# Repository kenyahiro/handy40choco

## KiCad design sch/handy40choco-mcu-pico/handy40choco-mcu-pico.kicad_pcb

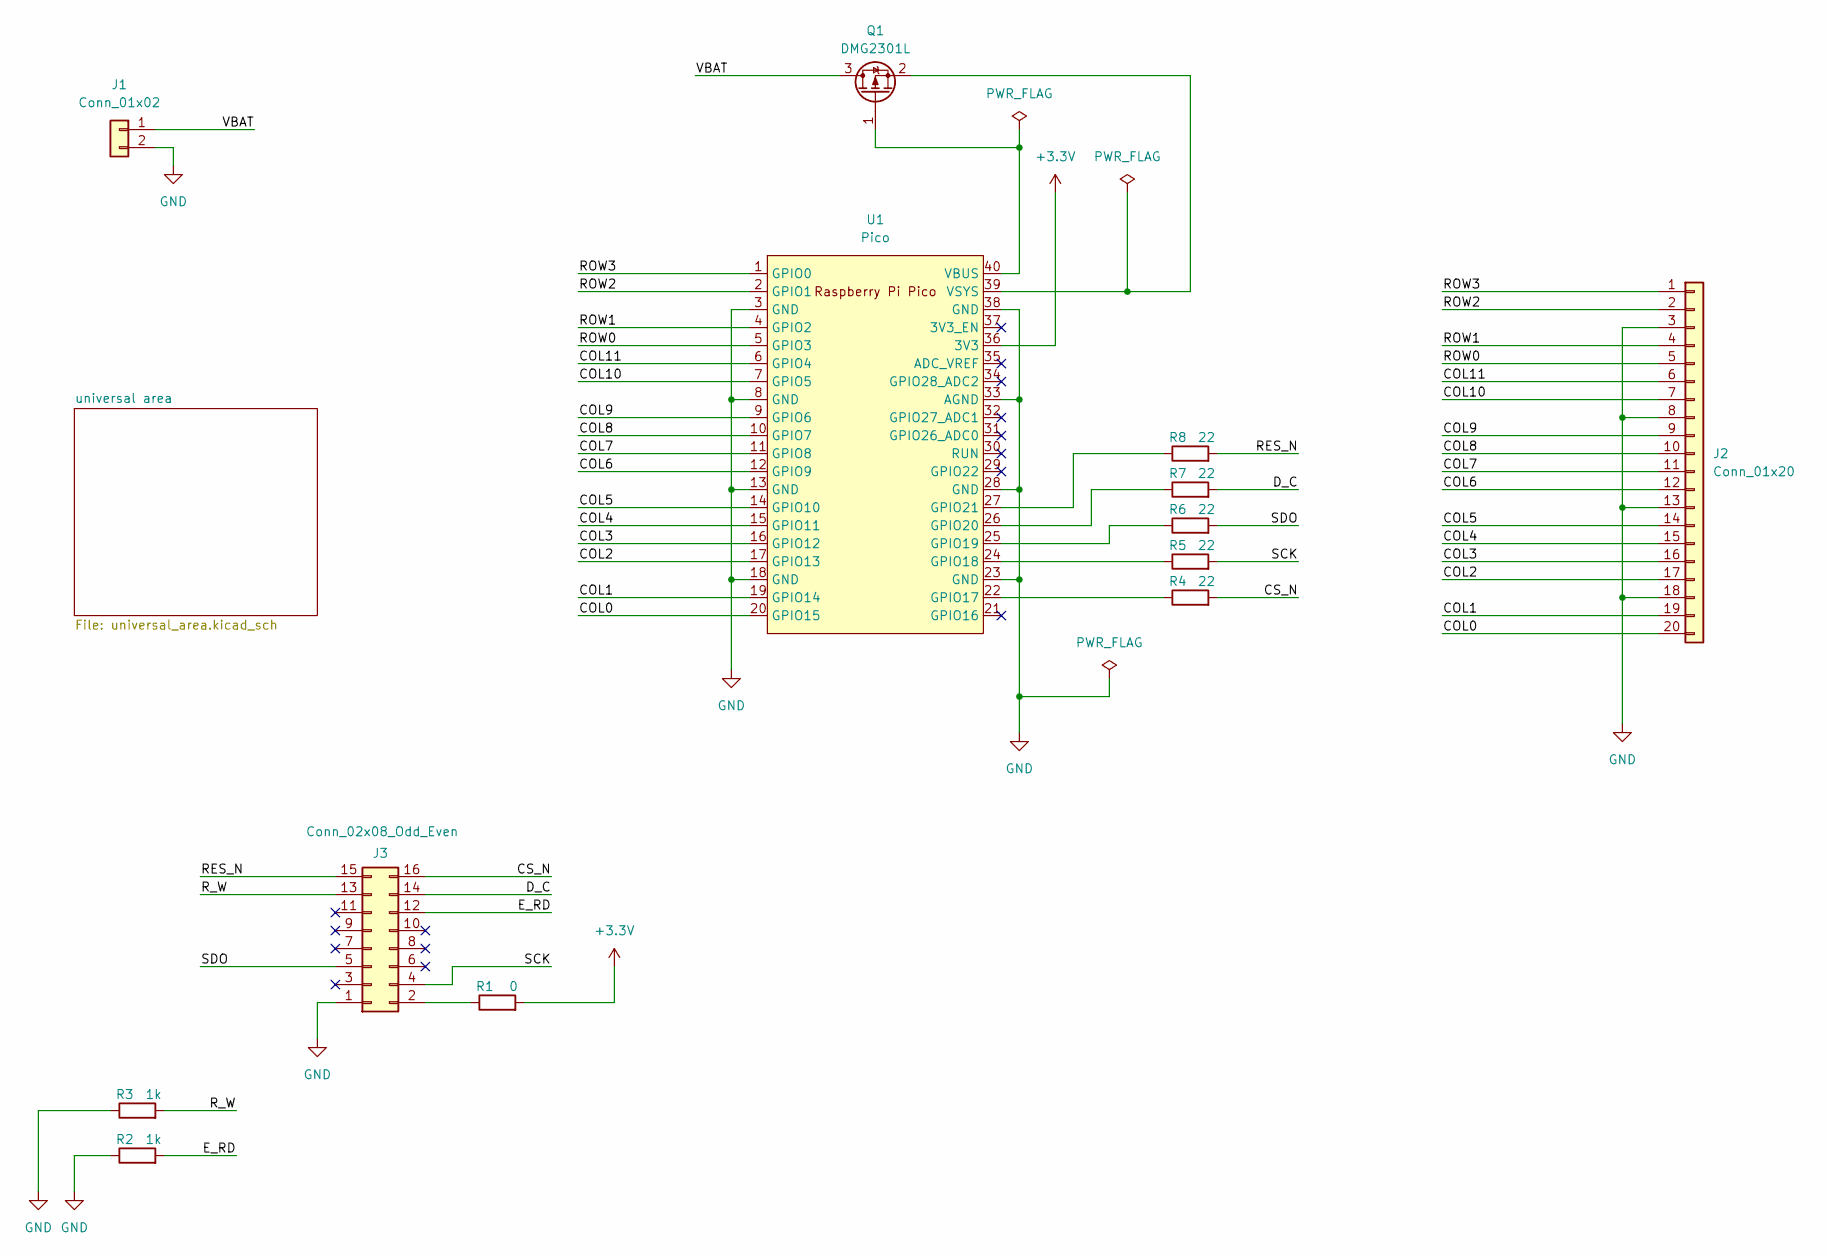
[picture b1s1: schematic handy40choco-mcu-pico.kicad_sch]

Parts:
J1: Conn_01x02; JST_PH_B2B-PH-K_1x02_P2.00mm_Vertical
J2: Conn_01x20; my_PinHeader_1x20_P2.54mm_Vertical_p0.85
J3: Conn_02x08_Odd_Even; oled_PinSocket_2x08_P2.54mm_Vertical
Q1: DMG2301L; SOT-23
R1: 0; R_0603_1608Metric_Pad0.98x0.95mm_HandSolder
R2, R3: 1k; R_0603_1608Metric_Pad0.98x0.95mm_HandSolder
R4, R5, R6, R7, R8: 22; R_0603_1608Metric_Pad0.98x0.95mm_HandSolder
U1: Pico; pico_no_dbg_smd_th_p0.85

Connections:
+3.3V: R1.2, U1.36 (3V3)
/COL0: J2.20, U1.20 (GPIO15)
/COL1: J2.19, U1.19 (GPIO14)
/COL2: J2.17, U1.17 (GPIO13)
/COL3: J2.16, U1.16 (GPIO12)
/COL4: J2.15, U1.15 (GPIO11)
/COL5: J2.14, U1.14 (GPIO10)
/COL6: J2.12, U1.12 (GPIO9)
/COL7: J2.11, U1.11 (GPIO8)
/COL8: J2.10, U1.10 (GPIO7)
/COL9: J2.9, U1.9 (GPIO6)
/COL10: J2.7, U1.7 (GPIO5)
/COL11: J2.6, U1.6 (GPIO4)
/CS_N: J3.16, R4.2
/D_C: J3.14, R7.2
/E_RD: J3.12, R2.2
/RES_N: J3.15, R8.2
/ROW0: J2.5, U1.5 (GPIO3)
/ROW1: J2.4, U1.4 (GPIO2)
/ROW2: J2.2, U1.2 (GPIO1)
/ROW3: J2.1, U1.1 (GPIO0)
/R_W: J3.13, R3.2
/SCK: J3.4, R5.2
/SDO: J3.5, R6.2
/VBAT: J1.1, Q1.3 (D)
GND: J1.2, J2.3, J2.8, J2.13, J2.18, J3.1, R2.1, R3.1, U1.3 (GND), U1.8 (GND), U1.13 (GND), U1.18 (GND), U1.23 (GND), U1.28 (GND), U1.33 (AGND), U1.38 (GND)
unnamed: J3.2, R1.1
unnamed: Q1.1 (G), U1.40 (VBUS)
unnamed: Q1.2 (S), U1.39 (VSYS)
unnamed: R4.1, U1.22 (GPIO17)
unnamed: R5.1, U1.24 (GPIO18)
unnamed: R6.1, U1.25 (GPIO19)
unnamed: R7.1, U1.26 (GPIO20)
unnamed: R8.1, U1.27 (GPIO21)

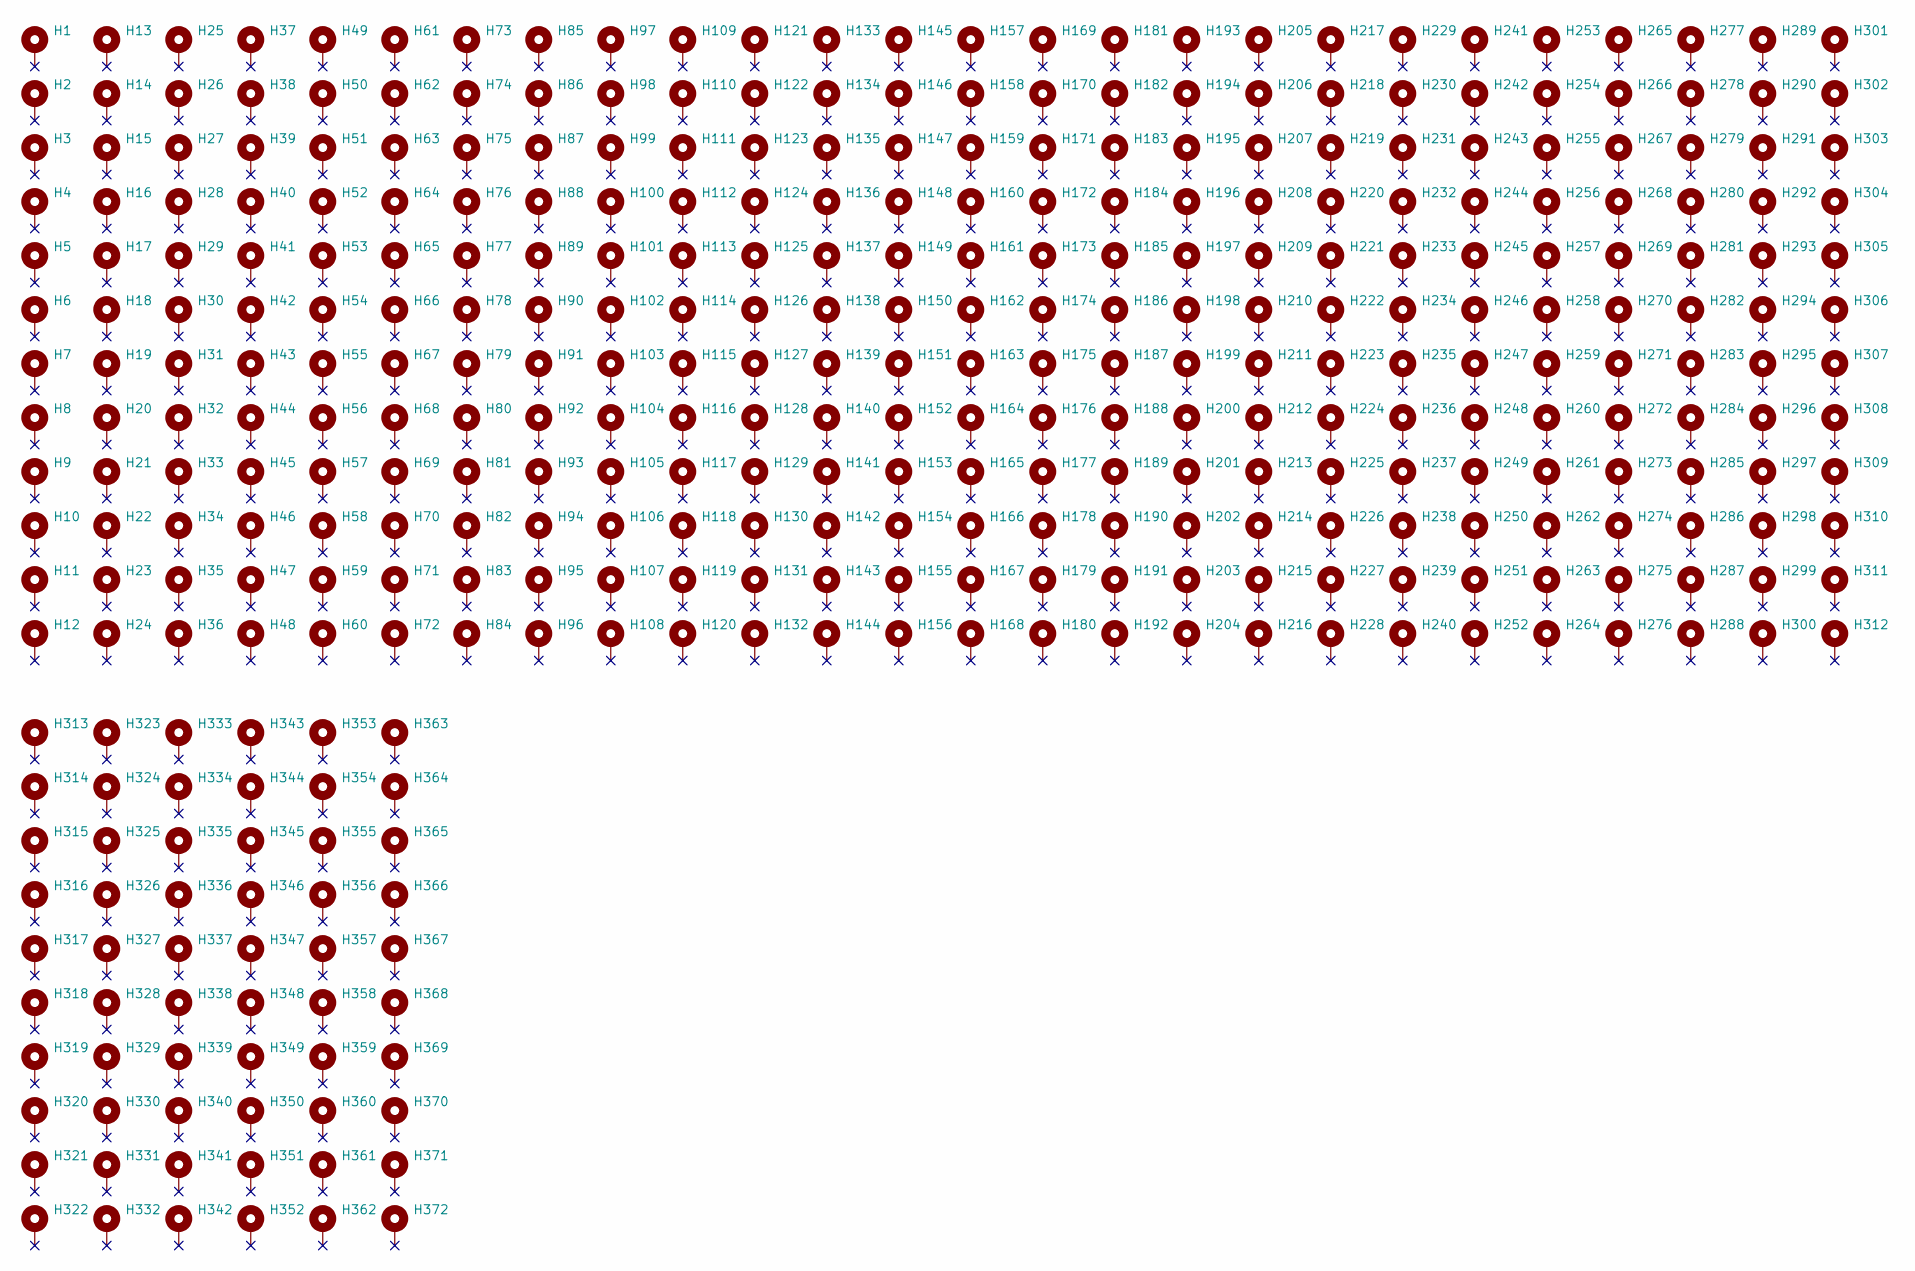
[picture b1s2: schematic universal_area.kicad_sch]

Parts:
H1, H2, H3, H4, H5, H6, H7, H8, H9, H10, H11, H12, H13, H14, H15, H16, H17, H18, H19, H20, H21, H22, H23, H24, H25, H26, H27, H28, H29, H30, H31, H32, H33, H34, H35, H36, H37, H38, H39, H40, H41, H42, H43, H44, H45, H46, H47, H48, H49, H50, H51, H52, H53, H54, H55, H56, H57, H58, H59, H60, H61, H62, H63, H64, H65, H66, H67, H68, H69, H70, H71, H72, H73, H74, H75, H76, H77, H78, H79, H80, H81, H82, H83, H84, H85, H86, H87, H88, H89, H90, H91, H92, H93, H94, H95, H96, H97, H98, H99, H100, H101, H102, H103, H104, H105, H106, H107, H108, H109, H110, H111, H112, H113, H114, H115, H116, H117, H118, H119, H120, H121, H122, H123, H124, H125, H126, H127, H128, H129, H130, H131, H132, H133, H134, H135, H136, H137, H138, H139, H140, H141, H142, H143, H144, H145, H146, H147, H148, H149, H150, H151, H152, H153, H154, H155, H156, H157, H158, H159, H160, H161, H162, H163, H164, H165, H166, H167, H168, H169, H170, H171, H172, H173, H174, H175, H176, H177, H178, H179, H180, H181, H182, H183, H184, H185, H186, H187, H188, H189, H190, H191, H192, H193, H194, H195, H196, H197, H198, H199, H200, H201, H202, H203, H204, H205, H206, H207, H208, H209, H210, H211, H212, H213, H214, H215, H216, H217, H218, H219, H220, H221, H222, H223, H224, H225, H226, H227, H228, H229, H230, H231, H232, H233, H234, H235, H236, H237, H238, H239, H240, H241, H242, H243, H244, H245, H246, H247, H248, H249, H250, H251, H252, H253, H254, H255, H256, H257, H258, H259, H260, H261, H262, H263, H264, H265, H266, H267, H268, H269, H270, H271, H272, H273, H274, H275, H276, H277, H278, H279, H280, H281, H282, H283, H284, H285, H286, H287, H288, H289, H290, H291, H292, H293, H294, H295, H296, H297, H298, H299, H300, H301, H302, H303, H304, H305, H306, H307, H308, H309, H310, H311, H312, H313, H314, H315, H316, H317, H318, H319, H320, H321, H322, H323, H324, H325, H326, H327, H328, H329, H330, H331, H332, H333, H334, H335, H336, H337, H338, H339, H340, H341, H342, H343, H344, H345, H346, H347, H348, H349, H350, H351, H352, H353, H354, H355, H356, H357, H358, H359, H360, H361, H362, H363, H364, H365, H366, H367, H368, H369, H370, H371, H372: MountingHole_Pad; TestPoint_THTPad_a

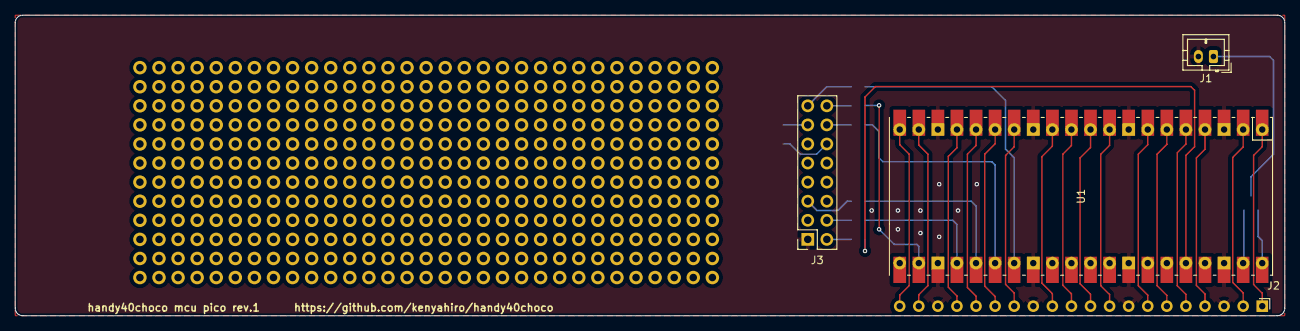
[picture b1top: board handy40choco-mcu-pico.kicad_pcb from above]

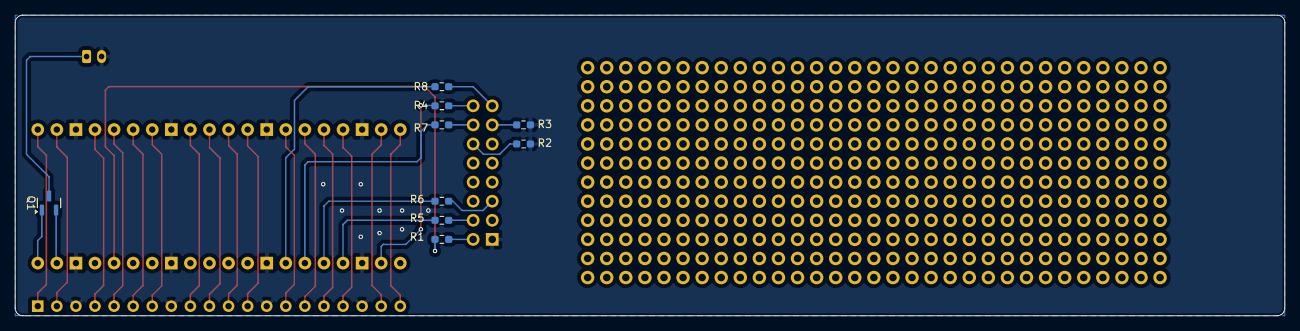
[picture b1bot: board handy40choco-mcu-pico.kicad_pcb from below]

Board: 2 copper layers, 169.0 x 40.0 mm, 385 parts (9 on the bottom side), 34 nets.

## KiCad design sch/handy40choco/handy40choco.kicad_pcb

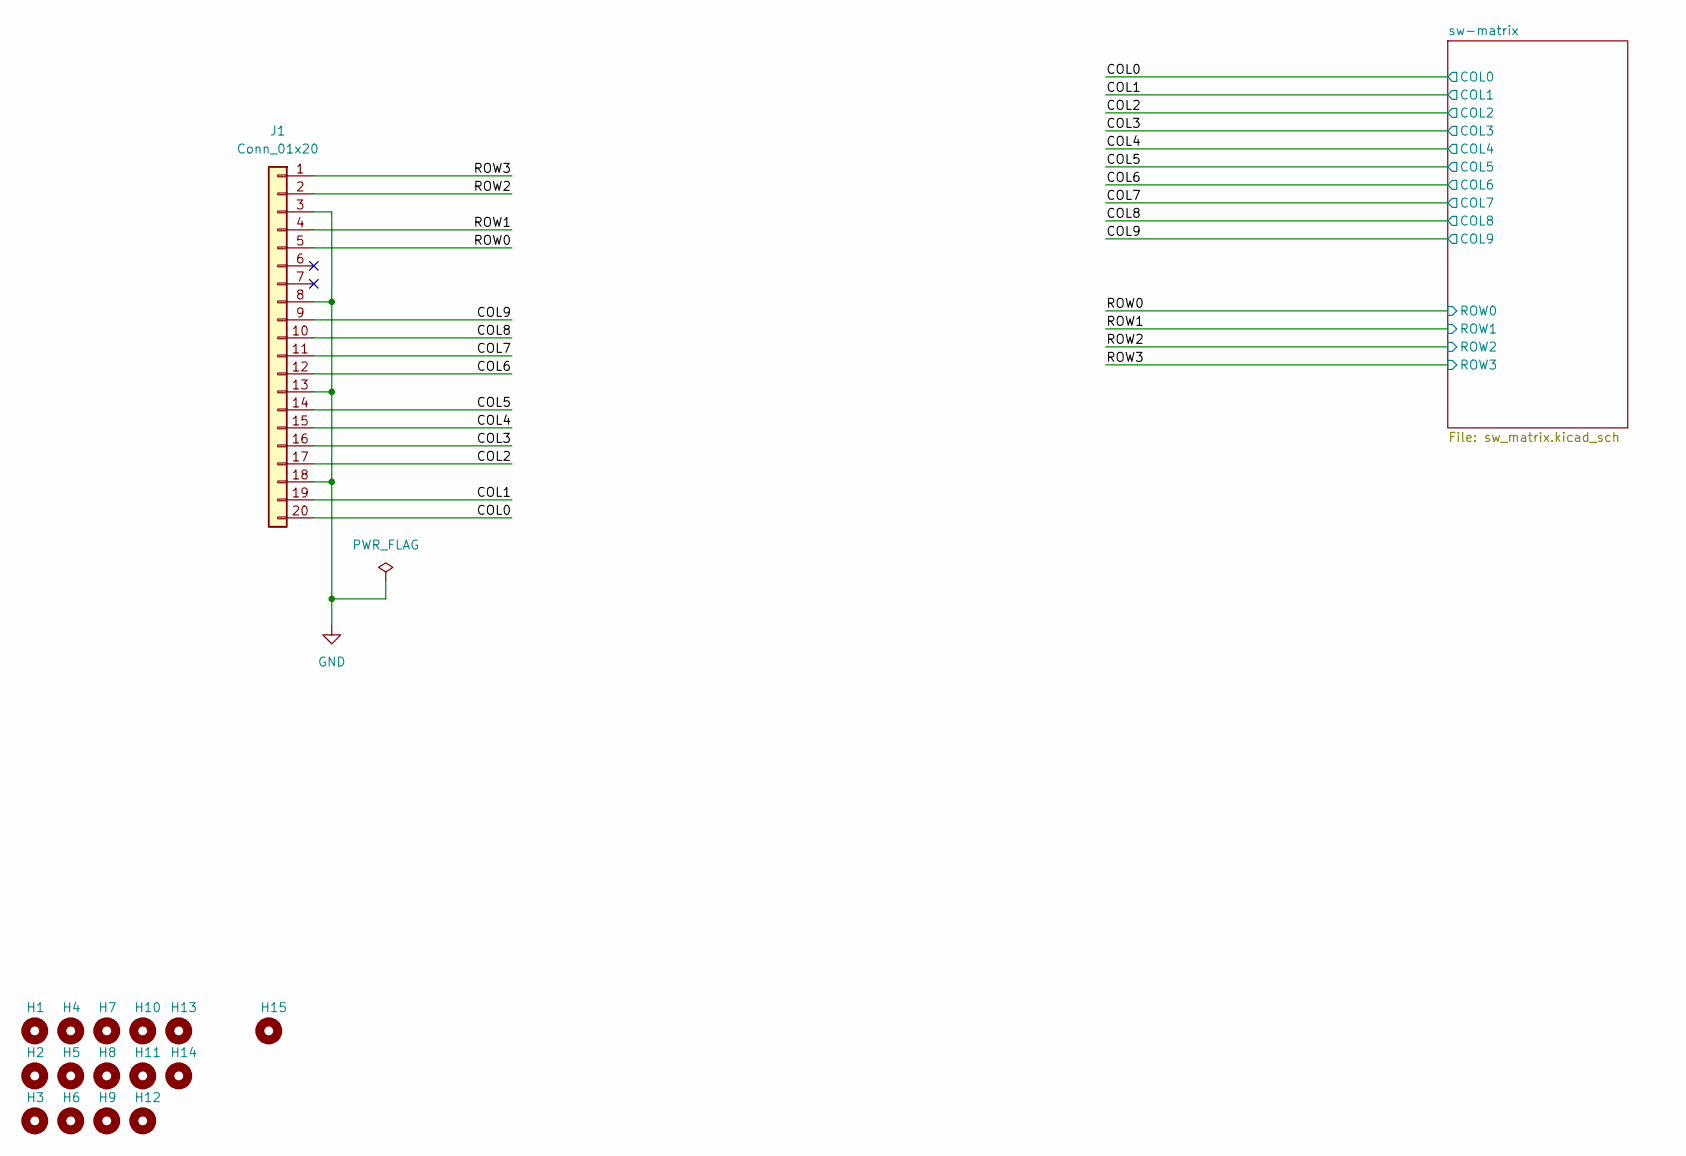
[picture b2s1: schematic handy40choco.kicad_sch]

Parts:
H1, H2, H3, H4, H5, H6, H7, H8, H9, H10, H11, H12, H13, H14, H15: MountingHole; my_MountingHole_2.2mm_M2
J1: Conn_01x20; my_PinHeader_1x20_P2.54mm_Vertical_p0.85

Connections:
/COL0: J1.20; also elsewhere on the board
/COL1: J1.19; also elsewhere on the board
/COL2: J1.17; also elsewhere on the board
/COL3: J1.16; also elsewhere on the board
/COL4: J1.15; also elsewhere on the board
/COL5: J1.14; also elsewhere on the board
/COL6: J1.12; also elsewhere on the board
/COL7: J1.11; also elsewhere on the board
/COL8: J1.10; also elsewhere on the board
/COL9: J1.9; also elsewhere on the board
/ROW0: J1.5; also elsewhere on the board
/ROW1: J1.4; also elsewhere on the board
/ROW2: J1.2; also elsewhere on the board
/ROW3: J1.1; also elsewhere on the board
GND: J1.3, J1.8, J1.13, J1.18

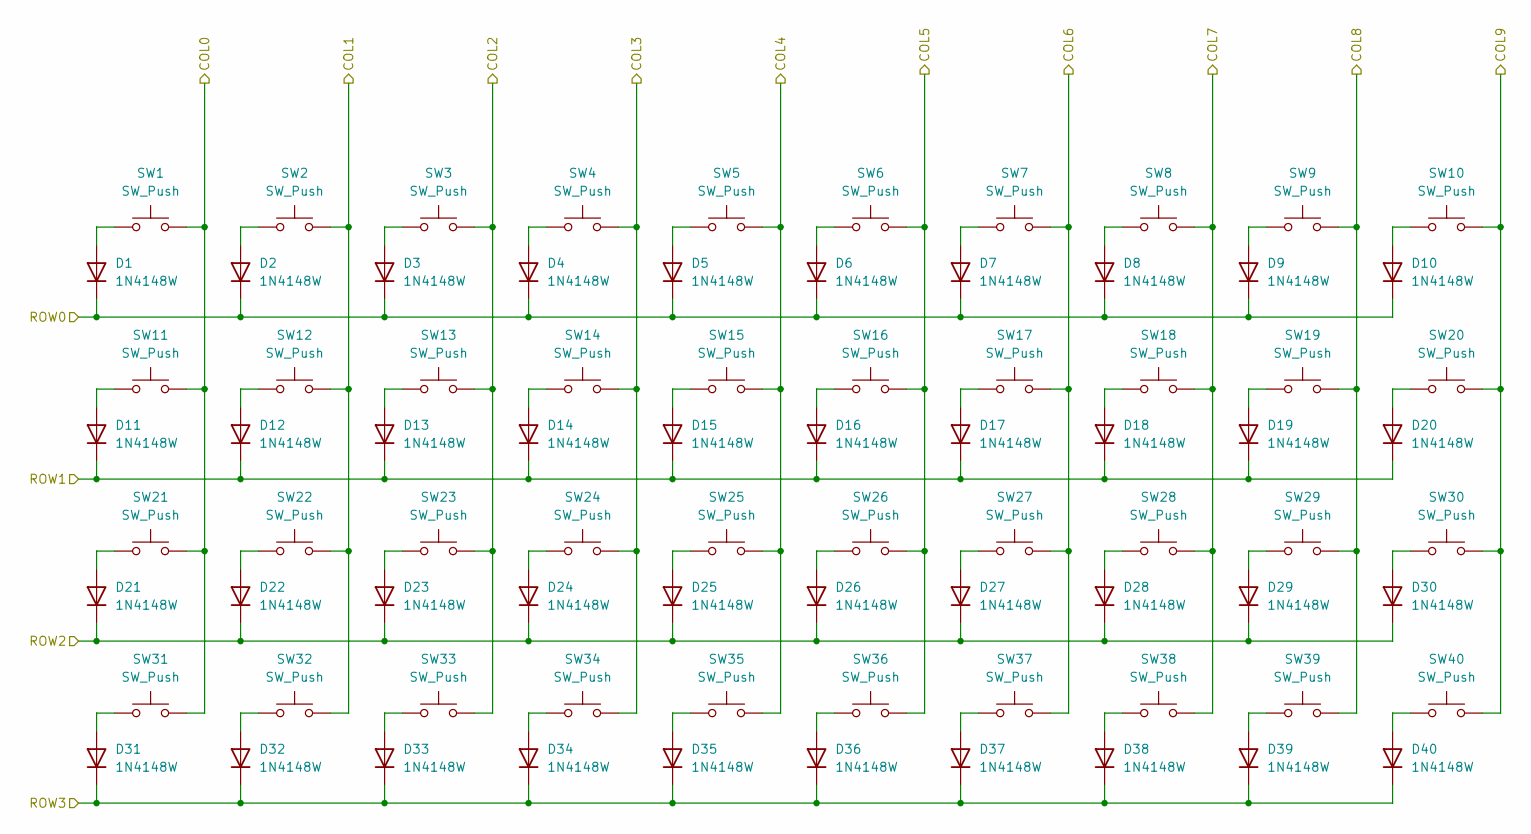
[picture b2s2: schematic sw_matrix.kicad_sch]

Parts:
D1, D2, D3, D4, D5, D6, D7, D8, D9, D10, D11, D12, D13, D14, D15, D16, D17, D18, D19, D20, D21, D22, D23, D24, D25, D26, D27, D28, D29, D30, D31, D32, D33, D34, D35, D36, D37, D38, D39, D40: 1N4148W; D_SOD-123
SW1, SW2, SW3, SW4, SW5, SW6, SW7, SW8, SW9, SW10, SW11, SW12, SW13, SW14, SW15, SW16, SW17, SW18, SW19, SW20, SW21, SW22, SW23, SW24, SW25, SW26, SW27, SW28, SW29, SW30, SW31, SW32, SW33, SW34, SW35, SW36, SW37, SW38, SW39, SW40: SW_Push; SW_Hotswap_Kailh_Choc_V1V2_no_mp

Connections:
/COL0: SW1.1, SW11.1, SW21.1, SW31.1; also elsewhere on the board
/COL1: SW2.2, SW12.2, SW22.2, SW32.2; also elsewhere on the board
/COL2: SW3.2, SW13.2, SW23.2, SW33.2; also elsewhere on the board
/COL3: SW4.2, SW14.2, SW24.2, SW34.2; also elsewhere on the board
/COL4: SW5.2, SW15.2, SW25.2, SW35.2; also elsewhere on the board
/COL5: SW6.2, SW16.2, SW26.2, SW36.2; also elsewhere on the board
/COL6: SW7.2, SW17.2, SW27.2, SW37.2; also elsewhere on the board
/COL7: SW8.2, SW18.2, SW28.2, SW38.2; also elsewhere on the board
/COL8: SW9.2, SW19.2, SW29.2, SW39.2; also elsewhere on the board
/COL9: SW10.2, SW20.2, SW30.2, SW40.2; also elsewhere on the board
/ROW0: D1.1 (K), D2.1 (K), D3.1 (K), D4.1 (K), D5.1 (K), D6.1 (K), D7.1 (K), D8.1 (K), D9.1 (K), D10.1 (K); also elsewhere on the board
/ROW1: D11.1 (K), D12.1 (K), D13.1 (K), D14.1 (K), D15.1 (K), D16.1 (K), D17.1 (K), D18.1 (K), D19.1 (K), D20.1 (K); also elsewhere on the board
/ROW2: D21.1 (K), D22.1 (K), D23.1 (K), D24.1 (K), D25.1 (K), D26.1 (K), D27.1 (K), D28.1 (K), D29.1 (K), D30.1 (K); also elsewhere on the board
/ROW3: D31.1 (K), D32.1 (K), D33.1 (K), D34.1 (K), D35.1 (K), D36.1 (K), D37.1 (K), D38.1 (K), D39.1 (K), D40.1 (K); also elsewhere on the board
unnamed: D1.2 (A), SW1.2
unnamed: D2.2 (A), SW2.1
unnamed: D3.2 (A), SW3.1
unnamed: D4.2 (A), SW4.1
unnamed: D5.2 (A), SW5.1
unnamed: D6.2 (A), SW6.1
unnamed: D7.2 (A), SW7.1
unnamed: D8.2 (A), SW8.1
unnamed: D9.2 (A), SW9.1
unnamed: D10.2 (A), SW10.1
unnamed: D11.2 (A), SW11.2
unnamed: D12.2 (A), SW12.1
unnamed: D13.2 (A), SW13.1
unnamed: D14.2 (A), SW14.1
unnamed: D15.2 (A), SW15.1
unnamed: D16.2 (A), SW16.1
unnamed: D17.2 (A), SW17.1
unnamed: D18.2 (A), SW18.1
unnamed: D19.2 (A), SW19.1
unnamed: D20.2 (A), SW20.1
unnamed: D21.2 (A), SW21.2
unnamed: D22.2 (A), SW22.1
unnamed: D23.2 (A), SW23.1
unnamed: D24.2 (A), SW24.1
unnamed: D25.2 (A), SW25.1
unnamed: D26.2 (A), SW26.1
unnamed: D27.2 (A), SW27.1
unnamed: D28.2 (A), SW28.1
unnamed: D29.2 (A), SW29.1
unnamed: D30.2 (A), SW30.1
unnamed: D31.2 (A), SW31.2
unnamed: D32.2 (A), SW32.1
unnamed: D33.2 (A), SW33.1
unnamed: D34.2 (A), SW34.1
unnamed: D35.2 (A), SW35.1
unnamed: D36.2 (A), SW36.1
unnamed: D37.2 (A), SW37.1
unnamed: D38.2 (A), SW38.1
unnamed: D39.2 (A), SW39.1
unnamed: D40.2 (A), SW40.1

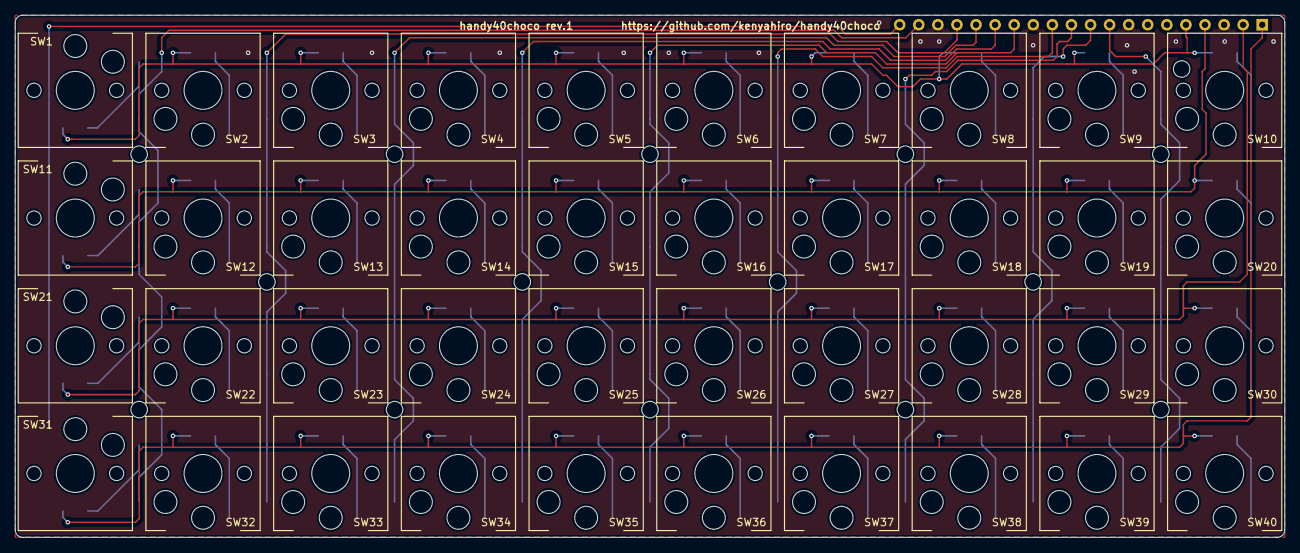
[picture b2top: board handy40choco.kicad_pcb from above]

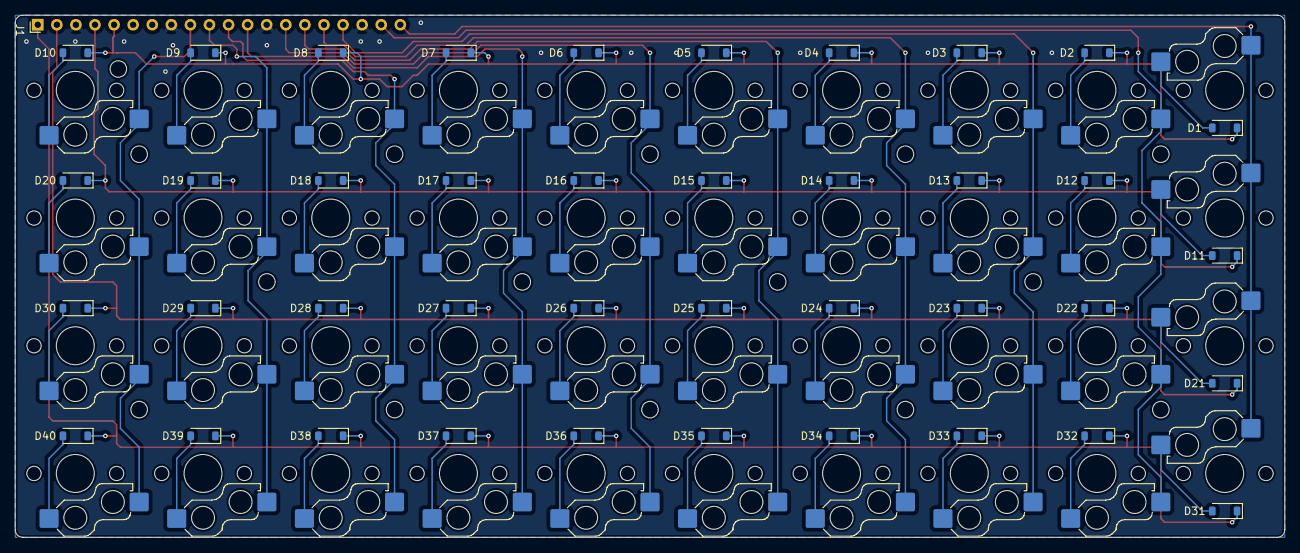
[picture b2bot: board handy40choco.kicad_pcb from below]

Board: 2 copper layers, 169.0 x 69.5 mm, 96 parts (41 on the bottom side), 55 nets.

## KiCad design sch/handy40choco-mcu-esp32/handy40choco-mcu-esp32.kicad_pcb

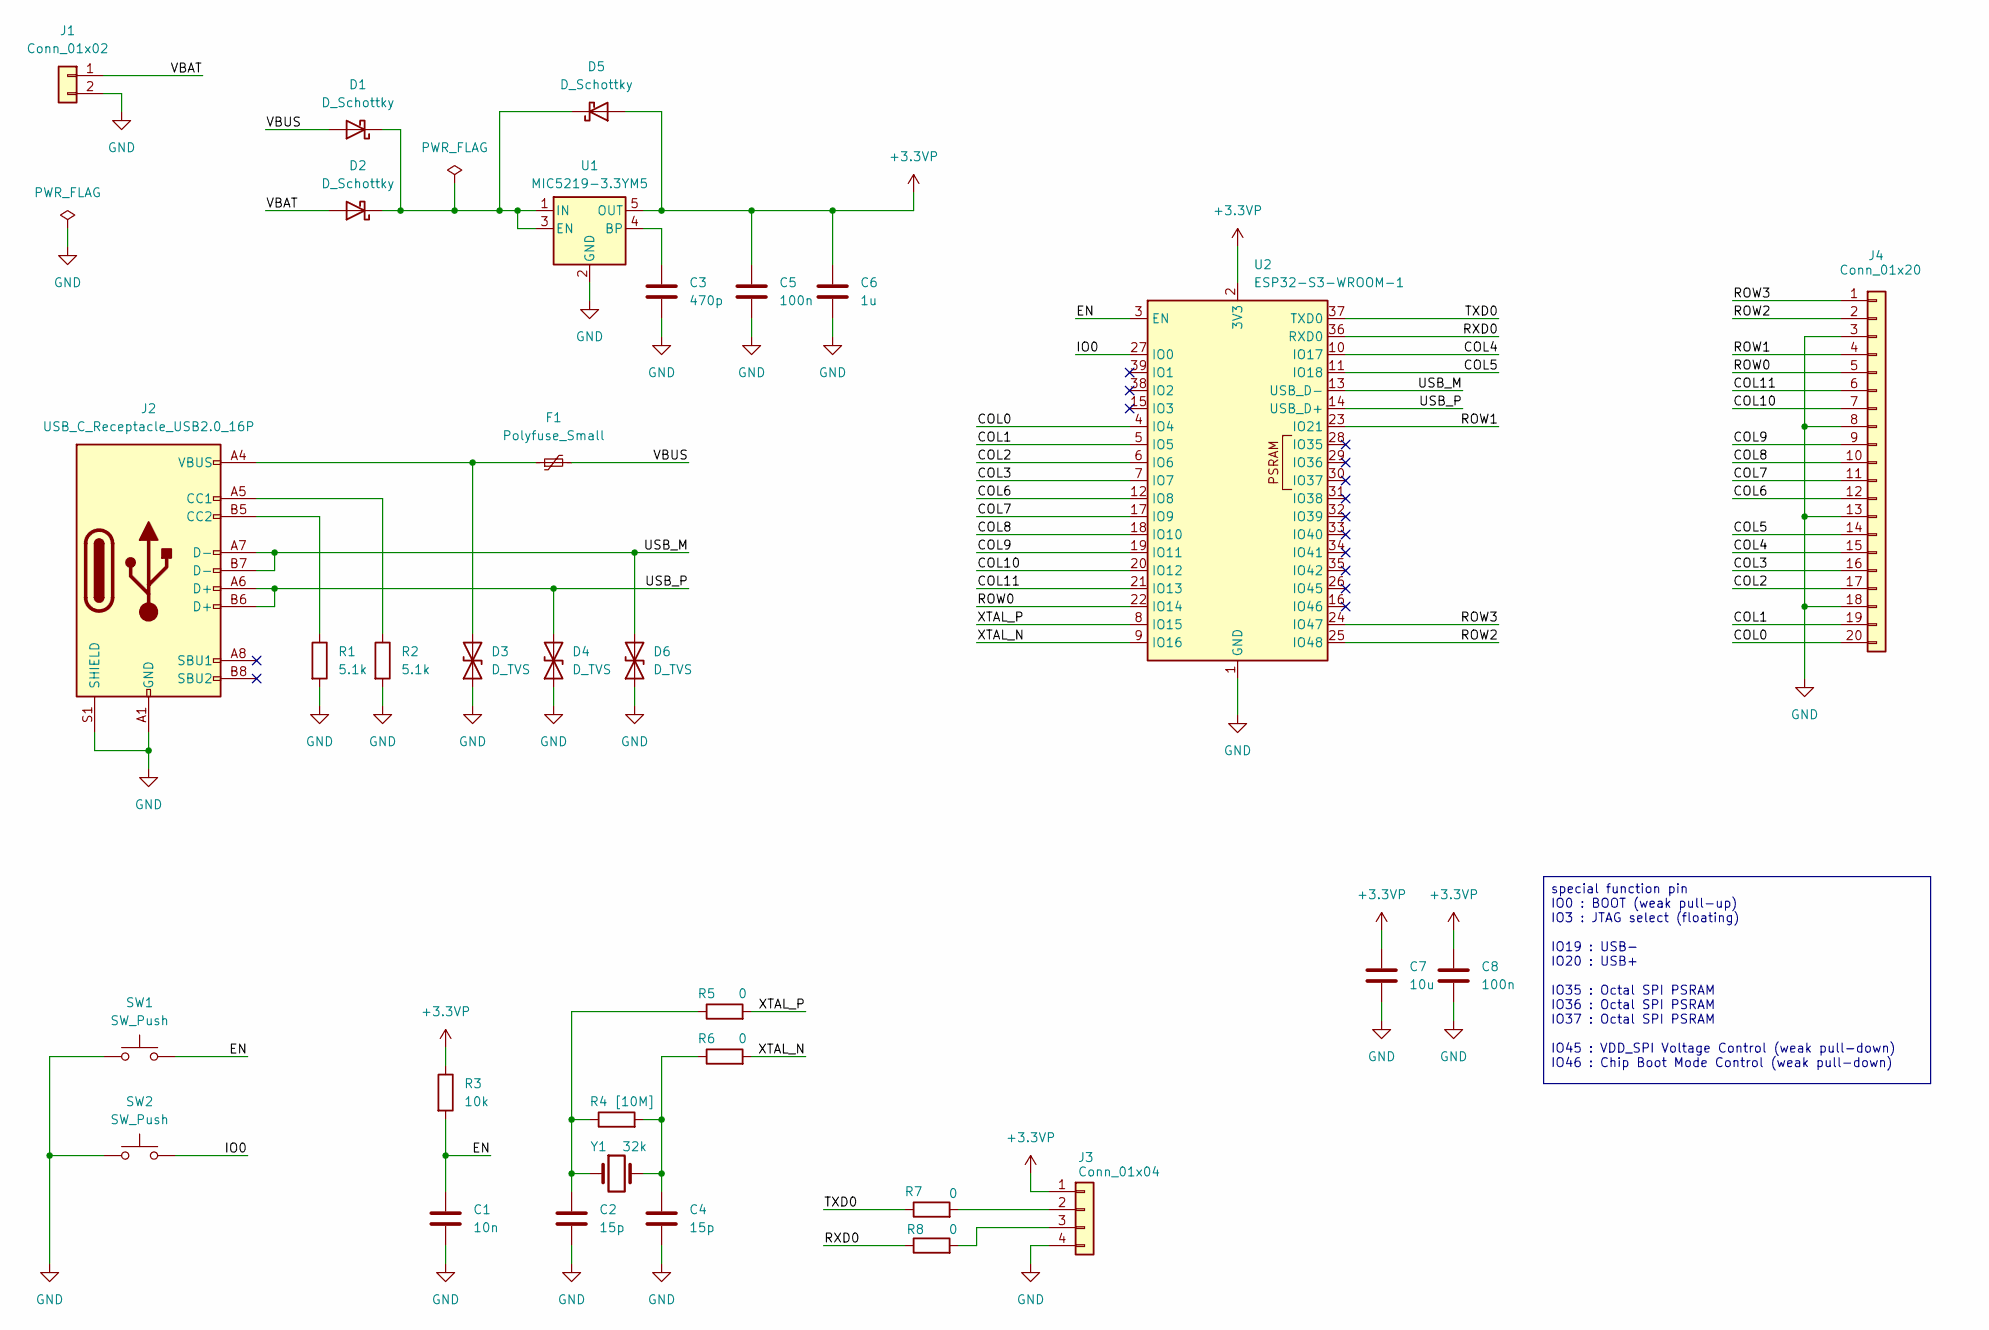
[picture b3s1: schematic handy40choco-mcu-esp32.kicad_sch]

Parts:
C1: 10n; C_0603_1608Metric_Pad1.08x0.95mm_HandSolder
C2, C4: 15p; C_0603_1608Metric_Pad1.08x0.95mm_HandSolder
C3: 470p; C_0603_1608Metric_Pad1.08x0.95mm_HandSolder
C5, C8: 100n; C_0603_1608Metric_Pad1.08x0.95mm_HandSolder
C6: 1u; C_0603_1608Metric_Pad1.08x0.95mm_HandSolder
C7: 10u; C_0603_1608Metric_Pad1.08x0.95mm_HandSolder
D1, D2, D5: D_Schottky; D_SOD-123
D3, D4, D6: D_TVS; D_SOD-123
F1: Polyfuse_Small; Fuse_Littelfuse-NANO2-451_453
J1: Conn_01x02; JST_PH_B2B-PH-K_1x02_P2.00mm_Vertical
J2: USB_C_Receptacle_USB2.0_16P; USB_C_Receptacle_XKB_U262-16XN-4BVC11
J3: Conn_01x04; JST_XH_B4B-XH-A_1x04_P2.50mm_Vertical
J4: Conn_01x20; PinHeader_1x20_P2.54mm_Vertical
R1, R2: 5.1k; R_0603_1608Metric
R3: 10k; R_0603_1608Metric
R4: [10M]; R_0603_1608Metric
R5, R6, R7, R8: 0; R_0603_1608Metric
SW1, SW2: SW_Push; SW_Push_SPST_NO_Alps_SKRK
U1: MIC5219-3.3YM5; SOT-23-5
U2: ESP32-S3-WROOM-1
Y1: 32k; Crystal_SMD_2012-2Pin_2.0x1.2mm_HandSoldering

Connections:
+3.3VP: C5.1, C6.1, C7.1, C8.1, D5.2 (A), J3.1, R3.1, U1.5 (OUT), U2.2 (3V3)
/COL0: J4.20, U2.4 (IO4)
/COL1: J4.19, U2.5 (IO5)
/COL2: J4.17, U2.6 (IO6)
/COL3: J4.16, U2.7 (IO7)
/COL4: J4.15, U2.10 (IO17)
/COL5: J4.14, U2.11 (IO18)
/COL6: J4.12, U2.12 (IO8)
/COL7: J4.11, U2.17 (IO9)
/COL8: J4.10, U2.18 (IO10)
/COL9: J4.9, U2.19 (IO11)
/COL10: J4.7, U2.20 (IO12)
/COL11: J4.6, U2.21 (IO13)
/EN: C1.1, R3.2, SW1.2, U2.3 (EN)
/IO0: SW2.2, U2.27 (IO0)
/ROW0: J4.5, U2.22 (IO14)
/ROW1: J4.4, U2.23 (IO21)
/ROW2: J4.2, U2.25 (IO48)
/ROW3: J4.1, U2.24 (IO47)
/RXD0: R8.1, U2.36 (RXD0)
/TXD0: R7.1, U2.37 (TXD0)
/USB_M: D6.2 (A2), J2.A7 (D-), J2.B7 (D-), U2.13 (USB_D-)
/USB_P: D4.2 (A2), J2.A6 (D+), J2.B6 (D+), U2.14 (USB_D+)
/VBAT: D2.2 (A), J1.1
/VBUS: D1.2 (A), F1.2
/XTAL_N: R6.2, U2.9 (IO16)
/XTAL_P: R5.2, U2.8 (IO15)
GND: C1.2, C2.2, C3.2, C4.2, C5.2, C6.2, C7.2, C8.2, D3.1 (A1), D4.1 (A1), D6.1 (A1), J1.2, J2.A1 (GND), J2.A12 (GND), J2.B1 (GND), J2.B12 (GND), J2.S1 (SHIELD), J3.4, J4.3, J4.8, J4.13, J4.18, R1.2, R2.2, SW1.1, SW2.1, U1.2 (GND), U2.1 (GND), U2.40 (GND), U2.41 (GND)
unnamed: C2.1, R4.1, R5.1, Y1.1
unnamed: C4.1, R4.2, R6.1, Y1.2
unnamed: D1.1 (K), D2.1 (K), D5.1 (K), U1.1 (IN), U1.3 (EN)
unnamed: D3.2 (A2), F1.1, J2.A4 (VBUS), J2.A9 (VBUS), J2.B4 (VBUS), J2.B9 (VBUS)
unnamed: J2.A5 (CC1), R2.1
unnamed: J2.B5 (CC2), R1.1
unnamed: J3.2, R7.2
unnamed: J3.3, R8.2
unnamed: C3.1, U1.4 (BP)

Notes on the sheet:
special function pin IO0 : BOOT (weak pull-up) IO3 : JTAG select (floating) IO19 : USB- IO20 : USB+ IO35 : Octal SPI PSRAM IO36 : Octal SPI PSRAM IO37 : Octal SPI PSRAM IO45 : VDD_SPI Voltage Control (weak pull-down) IO46 : Chip Boot Mode Control (weak pull-down)

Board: 2 copper layers, 32 parts (0 on the bottom side), 37 nets, no tracks yet.

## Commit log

2025-02-25 ハンディキーボードのたたき台です。
2025-05-08 pico, esp32-s3のマイコン基板の雛形のプロジェクトを追加しました。
2025-05-08 Kicad 9に変更しました。 マイコン基板から16ピンのピンヘッダに変更しました。
2025-05-08 未使用になった図面を削除しました。
2025-05-08 配線を完了しました。 シルクの位置を調整しました。
2025-05-08 電気図面のpdfを追加しました。 PCBのFABにピンヘッダの寸法線を追記しました。
2025-05-09 左端のキーの向きを180度回転させて、基板幅を短くしました。
2025-05-09 マイコン基板(pico)の雛形です。
2025-05-09 マイコン基板(ESP32-S3)の雛形です。
2025-05-13 ピンヘッダのフットプリントをコンスルーが使えるように、Φ0.85に変更しました。
2025-06-03 マイコンのピンヘッダの位置を基板端から1.27mmに移動しました。 COLの配線を部品面に移動しました。 基板サイズの微調整を行いました。
2025-06-11 OLEDのコネクタを追加しました。
2025-06-11 ユニバーサル領域を追加しました。
